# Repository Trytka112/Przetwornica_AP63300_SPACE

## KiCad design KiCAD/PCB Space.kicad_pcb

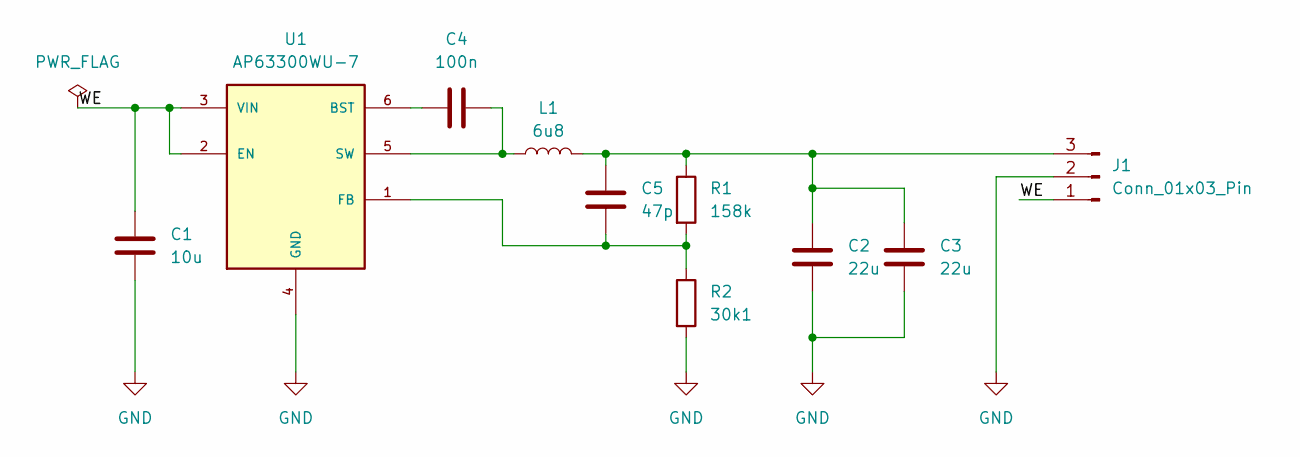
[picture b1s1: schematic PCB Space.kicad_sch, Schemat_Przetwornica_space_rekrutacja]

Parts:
C1: 10u; C_1206_3216Metric_Pad1.33x1.80mm_HandSolder
C2, C3: 22u; C_1206_3216Metric_Pad1.33x1.80mm_HandSolder
C4: 100n; C_0603_1608Metric_Pad1.08x0.95mm_HandSolder
C5: 47p; C_0603_1608Metric_Pad1.08x0.95mm_HandSolder
J1: Conn_01x03_Pin; PinHeader_1x03_P2.54mm_Vertical
L1: 6u8; L_Coilcraft_XAL7030-682
R1: 158k; R_0603_1608Metric_Pad0.98x0.95mm_HandSolder
R2: 30k1; R_0603_1608Metric_Pad0.98x0.95mm_HandSolder
U1: AP63300WU-7; SOT95P280X100-6N; PARTREV 2020-04-24

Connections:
/WE: C1.1, J1.1, U1.2 (EN), U1.3 (VIN)
GND: C1.2, C2.2, C3.2, J1.2, R2.2, U1.4 (GND)
unnamed: C2.1, C3.1, C5.1, J1.3, L1.2, R1.1
unnamed: C4.1, U1.6 (BST)
unnamed: C5.2, R1.2, R2.1, U1.1 (FB)
unnamed: C4.2, L1.1, U1.5 (SW)

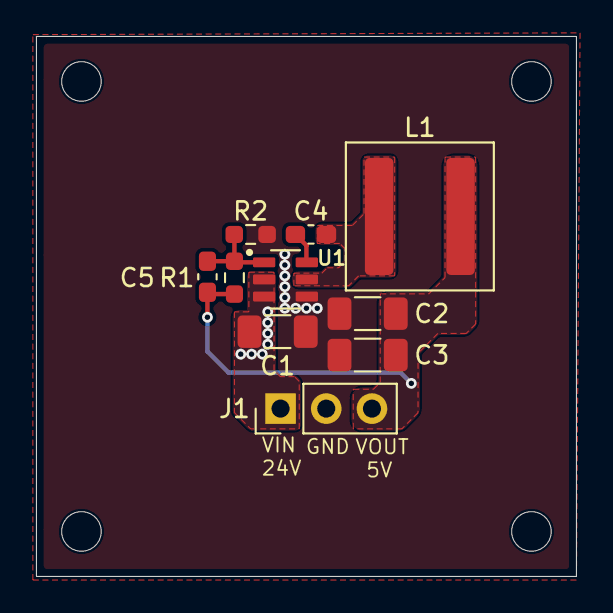
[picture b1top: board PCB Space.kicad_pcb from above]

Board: 2 copper layers, 30.0 x 30.0 mm, 10 parts (0 on the bottom side), 6 nets.
